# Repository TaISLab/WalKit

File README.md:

# WalKit

WalKit is an open hardware project created to monitor the elderly. It is modular, so different parameters, such as weight-bearing, cadence, activity duration, walking speed or other spatiotemporal gait parameters can be monitoring. 

- Packages in WalKit repository:
    - firmware: arduino codes for handles and wheels. 
    - hardware: 3d models and schematics.
    - walker_arduino: ros2 nodes to interact with USB arduino boards.   
    - walker_bringup: robot specific configuration scripts and tools. 
    - walker_centroid_support: obtains weight centroid based on current support.
    - walker_description: robot description.  
    - walker_diff_odom: odometry node.
    - walker_loads: reports partial supports on each leg.
    - walker_msgs: custom handle and wheel encoder msgs.
    - walker_navigation2: nav2 configuration for walker (TODO). 
    - walker_rviz: draws what the walker measures in rviz (handle loads, feet, support centroid, stability, gait) and holds the rviz views.
    - walker_simulation: roller simulation in gazebo.
    - walker_slam: (TODO)
    - walker_step_detector: reports step position.
    - walker_web_gui: web interface for tests.
            
- Other repositories the workspace uses (all in [`walker.repos`](walker.repos), see [Getting the sources](#getting-the-sources))
    - csm: ROS2 port of Andrea Censi's scan matcher, needed by the laser scan matcher package.
    - ros2_laser_scan_matcher: provides odometry from laser readings.
    - rplidar_ros: RPLidar A1 package.
    - witmotion_ros: driver of the WitMotion IMU.
    - slg_msgs, laser_segmentation: scan segmentation, used by the `seg` variant of walker_step_detector.
    - mocap4r2: MOCAP4ROS2 messages, visualisation and Vicon driver.
    - e4_msgs: messages of the Empatica E4 wristband.

<p align="right">(<a href="#top">back to top</a>)</p>

<!-- GETTING THE SOURCES -->
## Getting the sources

The public repositories the workspace is made of (WalKit itself, the sensor drivers, the laser odometry, the mocap messages...) are
listed in [`walker.repos`](walker.repos), in the native format of [vcstool](https://github.com/dirk-thomas/vcstool). Each key is the
path inside the workspace's `src` folder, and `version` is a branch, a tag or a commit:

```yaml
repositories:
  lidar/rplidar_ros:
    type: git
    url: https://github.com/Slamtec/rplidar_ros.git
    version: ros2
```

To get all of them into an empty workspace (WalKit included, so there is nothing to clone before):
```
sudo apt install python3-vcstool
mkdir -p ~/workspace/walker_ws/src && cd ~/workspace/walker_ws
vcs import src --input https://raw.githubusercontent.com/TaISLab/WalKit/jazzy/walker.repos
```
From a clone of WalKit it is `vcs import src < src/WalKit/walker.repos`. The destination folder (`src`) has to exist already. Then build the
workspace with colcon as usual.

| To... | Run |
|---|---|
| see what changed in every repository | `vcs status src` |
| update them all | `vcs pull src` |
| add the repositories that were added to the file, without touching the ones you have | `vcs import --skip-existing src < walker.repos` |
| download without history | `vcs import --shallow src < walker.repos` |
| check that every url and version of the file exists | `vcs validate --input walker.repos` |
| save the exact commits of your workspace (e.g. for an experiment) | `vcs export --exact src > workspace.repos` |

Things to know:
- **Do not use `--skip-existing` for the first import.** `witmotion_ros` brings an empty `witmotion-uart-qt` folder (its submodule), the file
  has an entry for that path, and `--skip-existing` skips folders that exist: it stays empty and `witmotion_ros` does not build. Use it to
  update, because it also leaves alone the repositories where you have checked out another branch; a plain `vcs import` over a workspace
  switches each repository back to its `version`.
- `witmotion/witmotion_ros/witmotion-uart-qt` is pinned to a commit (the one `witmotion_ros` has as a submodule), which `vcs validate`
  cannot verify without cloning. `--shallow` works with it.
- `vcs` prints a `pkg_resources` deprecation warning with recent setuptools: it is harmless.
- Commented-out entries are the repositories the workspace used before or does not use any more; removing the `#` at the start of their
  lines makes them valid entries.
- The mocap4w analysis tools are in private repositories and are not in this file; they are listed in `mocap4w.repos`, in the
  [mocap_analysis](https://github.com/MFernandezCarmona/mocap_analysis) repository (it needs access to that account). Import it after this one.
- The old `walker.rosinstall` (wstool format) is gone: `wstool` is deprecated and does not read `.repos` files.

<p align="right">(<a href="#top">back to top</a>)</p>

<!-- USAGE EXAMPLES -->
## Usage
The system can be launched with the following:
```
cd ~/workspace/walker_ws/src/WalKit/walker_bringup/tmule/
tmule -c walker.yaml launch
```
Every window of `walker.yaml` has the `core` tag, so `--tag core` starts the same. The session does not record a rosbag: to record one run
`ros2 launch walker_bringup bag_recorder.launch.py bag_name:=test01`: the bag is stored at `~/bagsFolder/<campaign>_tests_walker/test01`
(see [walker_bringup](walker_bringup/README.md#recording-a-test)).

ROS launch files can be monitored at the tmux session. You can attach to it with the following command:
```
tmux a -t walker_ros2
```

You may have noticed we use Marc-Hanheide's [TMuLE](https://github.com/marc-hanheide/TMuLE) program to configure and manage a [tmux](https://github.com/tmux/tmux) session running all the components. TMuLE can be installed with:
```
sudo -H pip3 install tmule
```

<p align="right">(<a href="#top">back to top</a>)</p>

<!-- CONTRIBUTING -->
## Contributing

If you have a suggestion that would make this better, please fork the repo and create a pull request. You can also simply open an issue with the tag "enhancement".
Don't forget to give the project a star! Thanks again!

1. Fork the Project
2. Create your Feature Branch (`git checkout -b feature/AmazingFeature`)
3. Commit your Changes (`git commit -m 'Add some AmazingFeature'`)
4. Push to the Branch (`git push origin feature/AmazingFeature`)
5. Open a Pull Request

<p align="right">(<a href="#top">back to top</a>)</p>

<!-- LICENSE -->
## License

This project is licensed under the Creative Commons Attribution 4.0 - see [LICENSE](https://github.com/TaISLab/WalKit/blob/master/LICENSE) file for details.

<p align="right">(<a href="#top">back to top</a>)</p>

<!-- CONTACT -->
## Contact

Manuel Fernandez-Carmona - [@ermanazas](https://twitter.com/ermanazas) - manolofc at gmail.com

Project Link: [https://github.com/TaISLab/WalKit/tree/humble](https://github.com/TaISLab/WalKit/tree/humble)

<p align="right">(<a href="#top">back to top</a>)</p>

<!-- ACKNOWLEDGMENTS -->
## Acknowledgments

This work is funded by [Programa Proyectos RETOS del Ministerio de Ciencia, Innovación y Universidades (SAVIA: Sistema de Autonomía Variable para movIlidad Asistida, Ref: RTI2018-096701-B-C21)](http://www.grupoisis.uma.es/index.php?option=com_jresearch&view=project&task=show&id=208&Itemid=18&lang=es) at Málaga University, Spain

[Plan Propio de la Universidad de Málaga (E3-PROYECTOS DE PRUEBA DE CONCEPTO (E3/02/18))](https://www.uma.es/servicio-de-investigacion/cms/menu/plan-propio-de-investigacion/?set_language=en) at Málaga University, Spain

This great readme is based on [Othneil Drew](https://github.com/othneildrew/Best-README-Template)'s README template.

<p align="right">(<a href="#top">back to top</a>)</p>

<!-- MARKDOWN LINKS & IMAGES -->
<!-- https://www.markdownguide.org/basic-syntax/#reference-style-links -->
[contributors-shield]: https://img.shields.io/github/contributors/TaISLab/WalKit
[contributors-url]: https://github.com/TaISLab/WalKit/graphs/contributors
[forks-shield]: https://img.shields.io/github/forks/TaISLab/WalKit
[forks-url]: https://github.com/TaISLab/WalKit/network/members
[stars-shield]: https://img.shields.io/github/stars/TaISLab/WalKit
[stars-url]: https://github.com/TaISLab/WalKit/stargazers
[issues-shield]: https://img.shields.io/github/issues/TaISLab/WalKit
[issues-url]: https://github.com/TaISLab/WalKit/issues
[license-shield]: https://img.shields.io/github/license/TaISLab/WalKit
[license-url]: https://github.com/TaISLab/WalKit/blob/master/LICENSE
[product-screenshot]: images/screenshot.png

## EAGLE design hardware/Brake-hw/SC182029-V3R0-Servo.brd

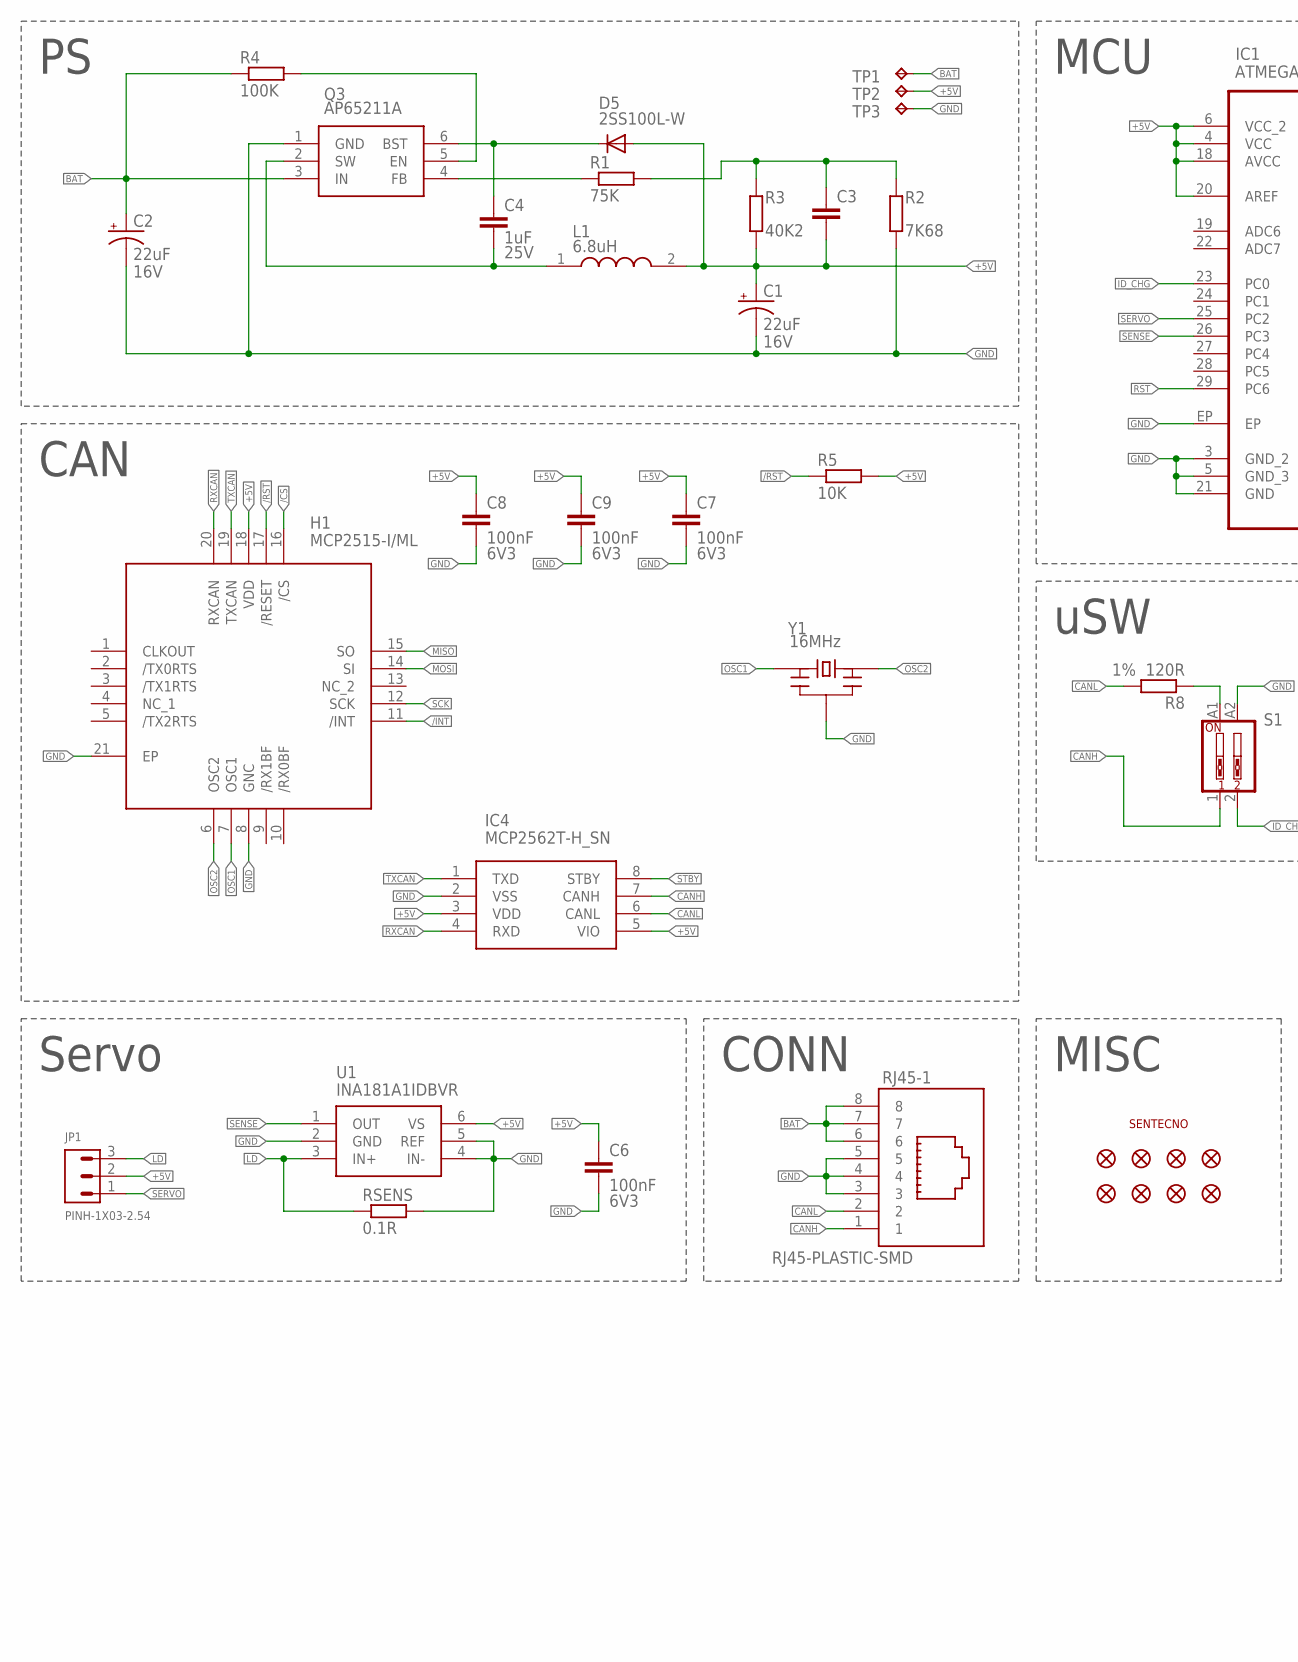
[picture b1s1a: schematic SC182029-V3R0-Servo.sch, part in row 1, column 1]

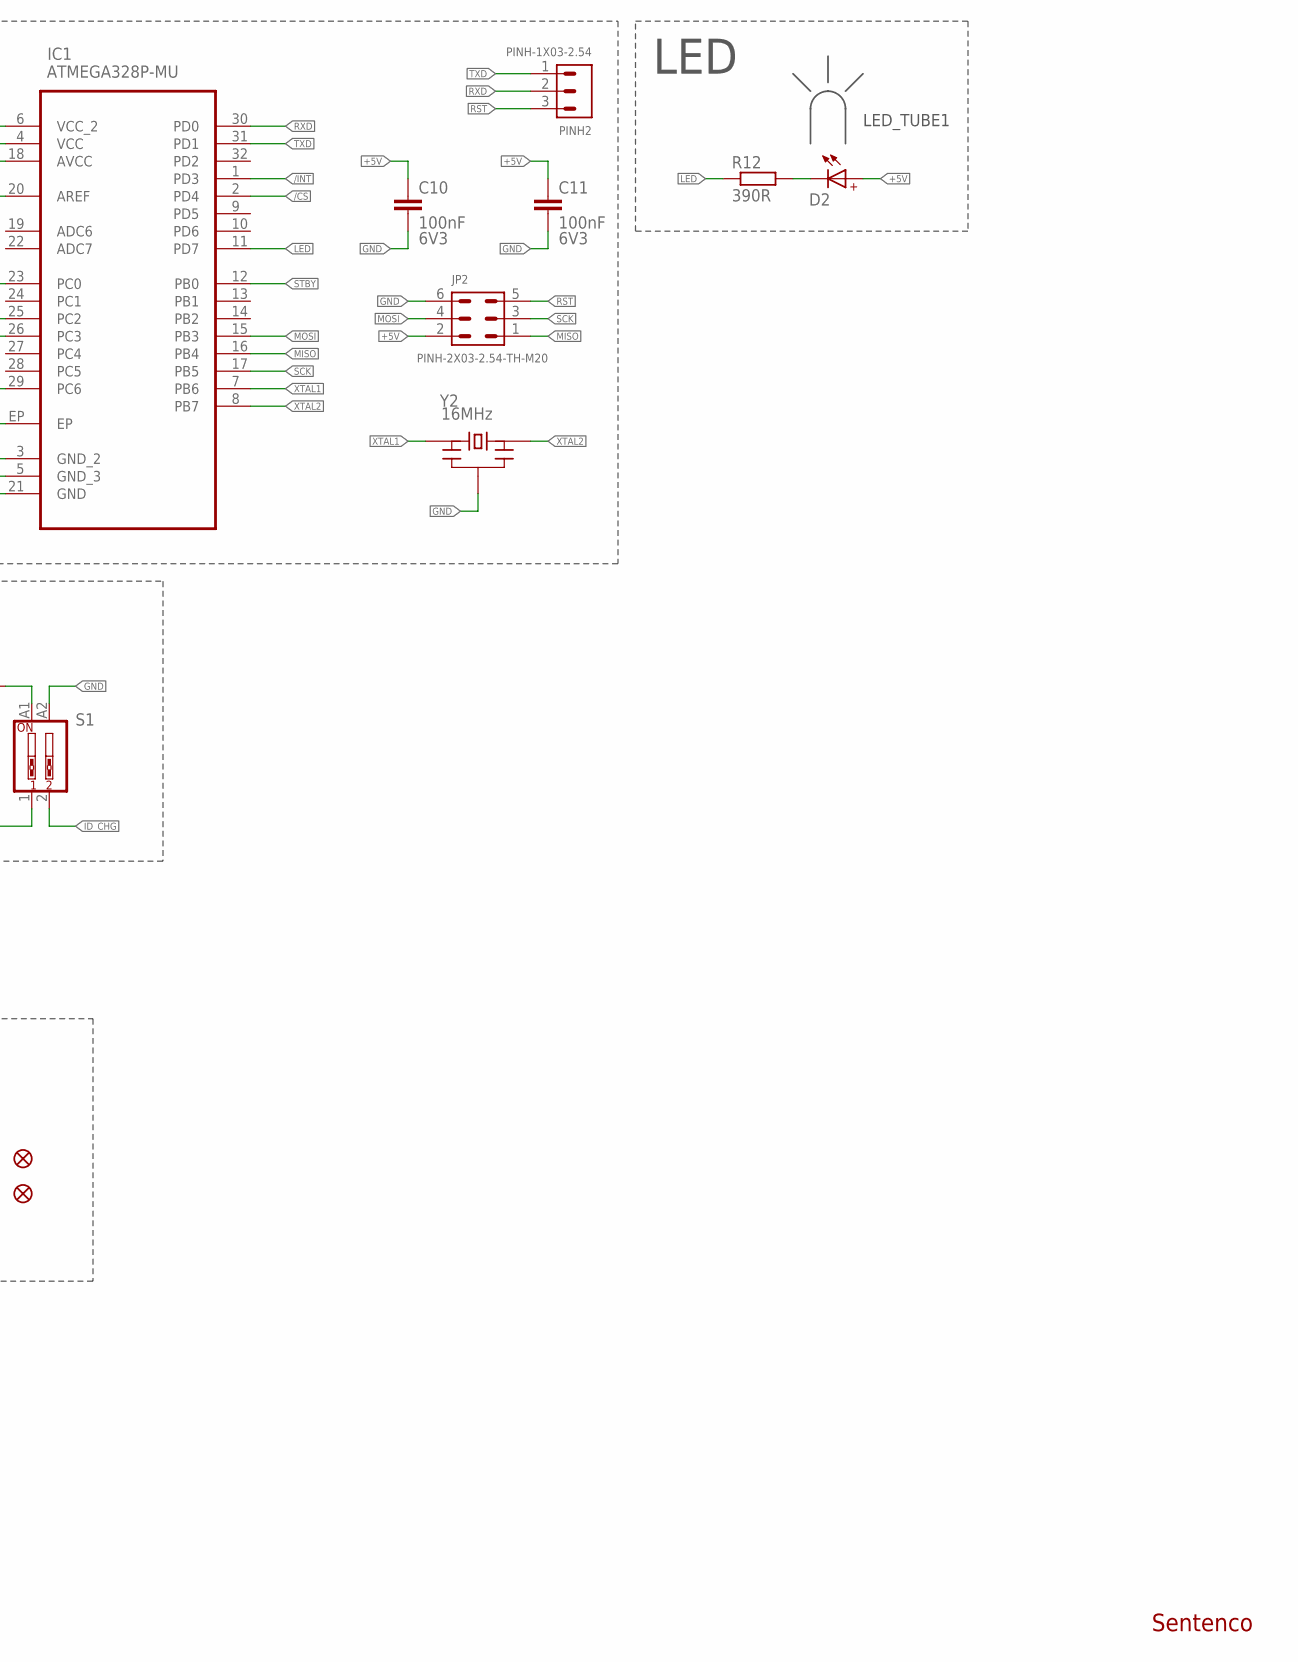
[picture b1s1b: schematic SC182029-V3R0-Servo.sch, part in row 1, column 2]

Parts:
C1, C2: 22uF; B
C3: COND_CERAMICO_SMD0603R; C0603R
C4: 1uF; C0603R
C6, C7, C8, C9, C10, C11: 100nF; C0603R
D2: WL-SMCW-150060BS75000; WL-SMCW_0603
D5: 2SS100L-W; SOD-123FL-CUSTOM
FID1, FID2, FID3, FID4, FID5, FID6, FID7, FID8: FIDUCIALUFIDUCIAL; MICRO-FIDUCIAL
H1: MCP2515-I/ML; QFN50P400X400X90-21N
IC1: ATMEGA328P-MU; QFN50P500X500X100-33N
IC4: MCP2562T-H_SN; SOIC127P600X175-8N
JP1: PINH-1X03-2.54; PINH-1X03-2.54-1
JP2: PINH-2X03-2.54-TH-M20; HDRV6W64P254_2X3_762X508X868P
L1: 6.8uH; NR5040
LED_TUBE1: LED_TUBEH1; LED_TUBE_2
LOGO1: LOGO_SENTECNOLOGO_6X4MM; LOGO_6X4MM
PINH2: PINH-1X03-2.54; PINH-1X03-2.54-1
Q3: AP65211A; SOT95P280X90-6N
R1: 75K; R0603R
R2: 7K68; R0603R
R3: 40K2; R0603R
R4: 100K; R0603R
R5: 10K; R0603R
R8: 120R; R0603R
R12: 390R; R0603R
RJ45-1: RJ45-PLASTIC-SMD; 73304111LF
RSENS: 0.1R; R0603R
S1: DIP-SW-2; SMD-DIP-SWITCH-2P
TP1, TP2, TP3: TPTP08R; TP0.8MMR
U1: INA181A1IDBVR; SOT95P280X145-6N
Y1, Y2: 16MHz; CSTNE16M0V530000R0

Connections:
+5V: C1.PIN_1_POS (+), C3.2, C6.1, C7.1, C8.1, C9.1, C10.1, C11.1, D2.2 (+), D5.+ (A), H1.18 (VDD), IC1.4 (VCC), IC1.6 (VCC_2), IC1.18 (AVCC), IC1.20 (AREF), IC4.3 (VDD), IC4.5 (VIO), JP1.2, JP2.2, L1.2, R3.1, R5.2, TP2.TP, U1.6 (VS)
/CS: H1.16 (/CS), IC1.2 (PD4)
/INT: H1.11 (/INT), IC1.1 (PD3)
/RST: H1.17 (/RESET), R5.1
BAT: C2.PIN_1_POS (+), Q3.3 (IN), R4.1, RJ45-1.6, RJ45-1.7, RJ45-1.8, TP1.TP
CANH: IC4.7 (CANH), RJ45-1.1, S1.1
CANL: IC4.6 (CANL), R8.2, RJ45-1.2
GND: C1.PIN_2_NEG (-), C2.PIN_2_NEG (-), C6.2, C7.2, C8.2, C9.2, C10.2, C11.2, H1.8 (GNC), H1.21 (EP), IC1.3 (GND_2), IC1.5 (GND_3), IC1.21 (GND), IC1.EP, IC4.2 (VSS), JP2.6, Q3.1 (GND), R2.1, RJ45-1.3, RJ45-1.4, RJ45-1.5, RSENS.2, S1.A2, TP3.TP, U1.2 (GND), U1.4 (IN-), U1.5 (REF), Y1.2 (GND), Y2.2 (GND)
ID_CHG: IC1.23 (PC0), S1.2
LD: JP1.3, RSENS.1, U1.3 (IN+)
LED: IC1.11 (PD7), R12.1
MISO: H1.15 (SO), IC1.16 (PB4), JP2.1
MOSI: H1.14 (SI), IC1.15 (PB3), JP2.4
unnamed: R8.1, S1.A1
unnamed: Q3.5 (EN), R4.2
unnamed: C4.1, D5.- (K), D5.-- (K), Q3.6 (BST)
unnamed: C4.2, L1.1, Q3.2 (SW)
unnamed: D2.1 (-), R12.2
unnamed: Q3.4 (FB), R1.1
unnamed: C3.1, R1.2, R2.2, R3.2
OSC1: H1.7 (OSC1), Y1.3 (OUT)
OSC2: H1.6 (OSC2), Y1.1 (IN)
RST: IC1.29 (PC6), JP2.5, PINH2.3
RXCAN: H1.20 (RXCAN), IC4.4 (RXD)
RXD: IC1.30 (PD0), PINH2.2
SCK: H1.12 (SCK), IC1.17 (PB5), JP2.3
SENSE: IC1.26 (PC3), U1.1 (OUT)
SERVO: IC1.25 (PC2), JP1.1
STBY: IC1.12 (PB0), IC4.8 (STBY)
TXCAN: H1.19 (TXCAN), IC4.1 (TXD)
TXD: IC1.31 (PD1), PINH2.1
XTAL1: IC1.7 (PB6), Y2.3 (OUT)
XTAL2: IC1.8 (PB7), Y2.1 (IN)

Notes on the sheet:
LED
MCU
Servo
CONN
CAN
MISC
uSW
Sentenco

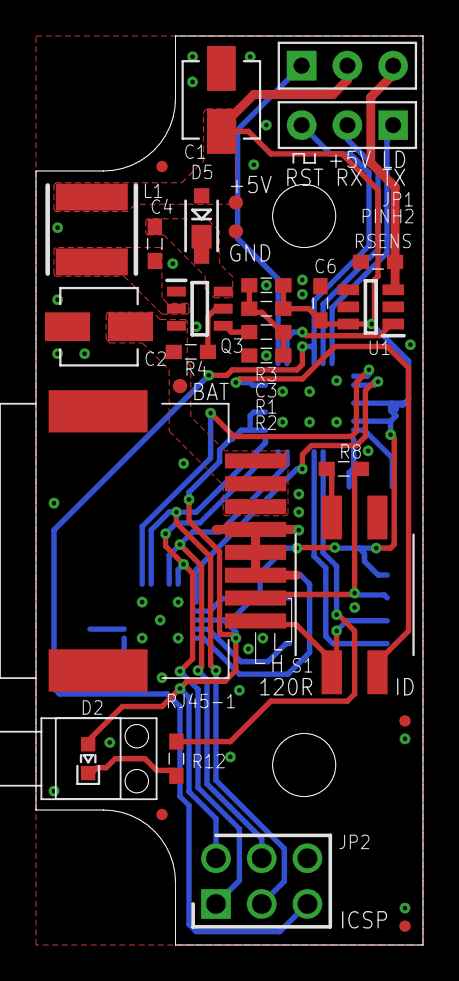
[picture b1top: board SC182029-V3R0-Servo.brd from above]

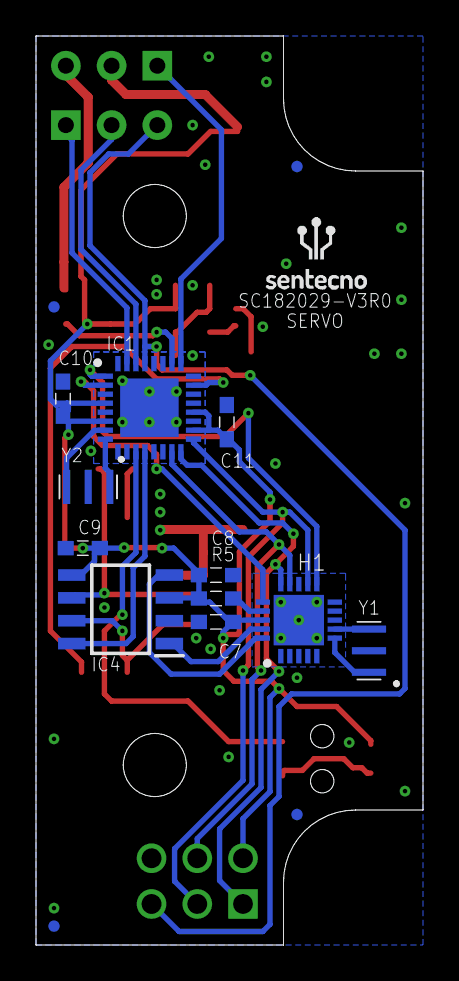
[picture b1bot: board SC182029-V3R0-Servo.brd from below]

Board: 2 copper layers, 21.5 x 50.5 mm, 46 parts (16 on the bottom side), 33 nets.

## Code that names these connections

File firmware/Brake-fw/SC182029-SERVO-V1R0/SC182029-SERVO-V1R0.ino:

/* ================================================================

   Proyecto: Modulo de encoder en andador para UMA
   Placa de desarrollo: Arduino
   Función: Gira entre 0 y 90 grados la posición del servo empujando
			el cable de freno, tiene un led indicador y envía los datos a
			través del BUS CAN.
			
   Autor: Justo Barroso Fontalba
   Fecha: 19/03/2019

   ================================================================ */

/* ================================================================
   Librerías
   ================================================================ */

#include <SPI.h>
#include <Servo.h>
#include <mcp_can.h>

/* ================================================================
   Definición de pines
   ================================================================ */

//ATMega328 TQFP
//                    Pin IDE //Pin puerto, Pin Físico
#define LED_GATE        7     //PD7, 11
#define MCP2515_STBY    8     //PB0, 12
#define MCP2515_CS      4     //PD4, 2
#define MCP2515_INT     3     //PD3, 1
#define SERVO           16    //PC2, 25
#define SENSE           17    //PC3, 26
#define ID_CHG          14    //PC0, 23
//#define MCP2515_SI      11    //PB3, 15
//#define MCP2515_SO      12    //PB4, 16
//#define MCP2515_SCK     13    //PB5, 17

//Test en Arduino UNO
//#define MCP2515_CS      10
//#define MCP2515_INT     2
//#define SERVO           3       //PD3, 5  (Arduino UNO)

//Constantes
#define ID_RIGHT      0x013   //Identificador del modulo derecho
#define ID_LEFT       0x023   //Identificador del modulo izquierdo
#define MAX_CURRENT   715     //Valor máximo de corriente en el servo 1.75A

/* ================================================================
   Definición de funciones
   ================================================================ */

/* ================================================================
   Definición de estructuras
   ================================================================ */

/* ================================================================
   Definición de variables
   ================================================================ */

static long unsigned int rxId; //Identificador del mensaje
static byte len = 0; //Longitud del mensaje
static byte rxBuf[8]; //Array datos de recepción
static byte txBuf[8] = { 0x00, 0x00, 0x00, 0xDD, 0x00, 0xFF, 0x00, 0x00 }; //Array datos de envió
static byte id_device = ID_LEFT;

/* ================================================================
   Drivers
   ================================================================ */

Servo servoMotor;

/* ================================================================
   Inicialización
   ================================================================ */

MCP_CAN CAN0( MCP2515_CS ); // Establece el CS en el pin 10

void setup() {
  //Configuración de pines
  pinMode( LED_GATE, OUTPUT );
  pinMode( SENSE, INPUT );
  pinMode( MCP2515_INT, INPUT_PULLUP ); // Interrupción MCP2515
  pinMode( MCP2515_STBY, OUTPUT ); // CS MCP2515  
  pinMode( ID_CHG, INPUT_PULLUP ); // Selección izquierda/derecha
  digitalWrite( MCP2515_STBY, LOW ); // Modo normal activo MCP2562

  //Establece la posición del modulo en el andador
  if ( digitalRead( ID_CHG ) == 0 ) {
    id_device = ID_RIGHT;
  }

  //Inicialización de puerto serie
  Serial.begin( 115200 );

  //Inicialización MCP2515, mascara y filtros activados, velocidad 500kb/s, cristal 16MHz
  if ( CAN0.begin( MCP_STDEXT, CAN_500KBPS, MCP_16MHZ ) == CAN_OK ) {
    Serial.println( "MCP2515 Initialized Successfully!" );
  }
  else {
    Serial.println( "Error Initializing MCP2515..." );
  }

  //Establece mascaras y filtros para los dispositivos
  CAN0.init_Mask( 0, 0, 0x001F0000 ); // Iniciando primera mascara
  CAN0.init_Filt( 0, 0, 0x00100000 ); // Iniciando primer filtro, ID 0x10 (rPi)

  CAN0.init_Mask( 1, 0, 0x001F0000 ); // Iniciando segunda mascara

  //Configuración del MCP2515
  CAN0.setMode( MCP_NORMAL ); // Modo normal para permitir el envio de mensajes

  //Configuración de pines
  servoMotor.attach( SERVO );

  //Establecer el angulo a 0
  servoMotor.write( 150 );

  //Configurando la interrupción por pin
  attachInterrupt( digitalPinToInterrupt( MCP2515_INT ), readCAN, LOW );

  for (int i = 0; i < 3; i++)
  {
    digitalWrite( LED_GATE, LOW );
    delay(200);
    digitalWrite( LED_GATE, HIGH );
    delay(200);
  }
}

/* ================================================================
   Bucle principal
   ================================================================ */

void loop() {
  
}

/* ================================================================
   Interrupciones
   ================================================================ */

void readCAN() {
  CAN0.readMsgBuf( &rxId, &len, rxBuf ); // Leer datos: len = longitud de los datos, buf = bytes de datos
  if ( rxBuf[0] == id_device ) {
    if ( ( rxBuf[1] & 0b00000001 ) == 0b00000001 ) {
      //if ( ( PIND & B10000000 ) == B00000000 ) {
        digitalWrite( LED_GATE, LOW ); //Enciende el LED
        Serial.println( "Led encendido" );
      //}
    }
    if ( ( rxBuf[1] & 0b00000001 ) == 0b00000000 ) {
      //if ( ( PIND & B10000000 ) == B00000100 ) {
        digitalWrite( LED_GATE, HIGH ); //Apaga el LED
        Serial.println( "Led apagado" );
      //}
    }
    //Rango operativo del servo entre 70 y 150 o 0x46 (90 grados) y 0x96 (0 grados)
    if ( ( rxBuf[1] & 0b00000010 ) == 0b00000010 ) {
      if ( rxBuf[2] <= 0x96 && rxBuf[2] >= 0x46 ) {
        servoMotor.write( rxBuf[2] ); //valor al servo
        //Serial.println( analogRead( SENSE ) );
        while ( analogRead( SENSE ) >= MAX_CURRENT ) {
          servoMotor.write( rxBuf[2] -= 0x05 );
          Serial.println( "Se ha reducido la fuerza ejercida sobre el freno." );
        }        
      }
      Serial.println( "Valor establecido: " );
      Serial.println( rxBuf[2] );
    }
  }
}

/* ================================================================
   Funciones
   ================================================================ */

/* ================================================================
   Fin
   ================================================================ */

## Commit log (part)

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2020-02-11 Create LICENSE
2021-11-22 WIP: sorting out new ros2 - foxy branch - created msg for Handle forces - created usb publisher node with launcher (TODO: parametrise published data int/double) TODO: upload Arduino codes for handles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
2021-11-24 WIP! - walker_arduino - reads data from usb arduinos and publishes it - TODO: - TEST!
    - walker_bringup
    - main package to start robot/spawn simulated robot
    - should call to walker_description, diff_odom, handles, lidars, etc ...
    - TODO:
    - think possible migration to param file
    - finish udev rules to ease serial port access
2021-11-24 added simulated worlds
2021-11-24 New arduino codes. Removed windows garbage
2021-11-24 First working version of Arduino devices
2021-11-25 m.ch.
2021-11-25 Removed submodule. It's easier to use separated repos
2021-11-29 limited number of tested chars
2021-11-29 debug info added
2021-11-29 Changed from stream buffers to use timeouts
2021-11-29 Can't find elegant solution to autodiscovery
2021-11-29 adding stuff
2021-11-29 WIP: walker_diff_odom
2021-11-30 Each device has now an udev rule for easier launch
2021-11-30 parameters adjusted but left wheel is still quite faulty
2021-11-30 laser launch file with custom params
2021-12-01 Rosinstall file added
2021-12-10 WIP: fixing odometry
2021-12-10 diff_odom: working version bringup: - tmule script also records data now - lasers are filtered for self collisions
2021-12-13 Added record to tmule script Added simple force plotter
2021-12-14 - Added config for laser filtering out leg detections - Added tmule file tags to avoid default recording - Added mapper config
2021-12-14 added reasonable tf for leapmotion
2021-12-16 typo
2021-12-17 Added leg detector repo
2021-12-17 Added laser_filters
2021-12-20 Filters is forked to support "inside box" filters
2021-12-20 added leg detector
2021-12-21 fire
2022-01-12 Odometry hardware was in wrong place
2022-01-16 Added detected steps to tmule file Removed bag reader script for more specific ones with plotting Created bag replay launchers to create additional topic bags
2022-01-17 WIP: partial load analysis
2022-01-17 first attempt for partial load node
2022-01-18 Better analysis pipeline
2022-01-19 Sorting and creating plotter
2022-01-24 WIP: playing with plot loads...
2022-01-26 MAYOR CHANGES! - no more leg_detector_msgs. Now all in walker_msgs - one topic per step, no more arrays - moved step_detector to Walkit and renamed to walker_step_detector
2022-01-26 params
2022-02-01 laser filter changed
2022-02-01 cleaning
2022-02-02 initial config
2022-02-08 Added vanilla odometry error
2022-02-08 bug including eigen
2022-02-08 adding covariance to odometry
2022-02-15 working on new odom and gait params
2022-02-16 bugs
2022-02-17 recording leapmotion too
2022-02-18 Working on gait param analysis
2022-03-09 ROS2 new version
2022-04-04 Demo changes
2022-04-04 m.ch
2022-04-06 Corrected handle position in crappy yaml Commented Step msg Added weight centroid calculus in partial loads
2022-05-04 WIP: including kalman filter for leg tracking
2022-05-05 working on kalman
2022-05-09 WIP: improve TF tree
2022-05-09 WIP: centroid module
2022-05-10 kalman filter embedded into step detector. Not ideal, but it works
2022-05-10 Added markers for visualization ...
2022-05-11 added csv debug output: we are detecting far few clusters...
2022-05-16 laser filters and leg detector removed
2022-05-16 Checking lsm
2022-05-16 Removing binaries from repo
2022-05-16 lcm works. EKF is not reading data for some reason ...
2022-05-17 friday
2022-05-17 Looks like it's working now
2022-05-18 debug prints commented
2022-05-18 All seems to work, but rviz debug is laggy
2022-05-19 testing centroid module
2022-05-20 centroid support module done
2022-05-23 WIP: Gui improvement
2022-05-23 Enc odom is no longer default
2022-05-23 improving tf
2022-05-23 mch2
2022-05-23 New robot model. New tf tree. New gui. Needs some testing
2022-06-10 Almost there
2022-06-13 First working version
2022-06-14 load detector with kalman filter seems to be working
2022-06-15 User description as a latched topic
2022-06-16 added modules to yaml
2022-06-21 python nodes now don't overreact to Ctrl+C Handle calibration only present at walker_loads. New msgs for gait params
2022-06-29 rule with all sensors
2022-07-04 Fixing install deps. Adding vars to gui. Publishing config data periodically
2022-07-04 did I messed it again?
2022-07-19 WIP: improving representation
2022-07-21 WIP: working on demo view
2022-07-21 WIP: less verbose output while waiting for all data
2022-07-21 Less verbose output. TF is published every 500ms
2022-07-21 Added handle load publisher (kg)
2022-07-21 Added live plot with - leg position (with loads) - laser in active area - handles (with loads)
2022-07-21 Publishing a stampedPose list of laser points to be used in gui. Active area is now filtered by step detector itself. Adding kalman multiple clusters adds half and half.
2022-07-21 added library
2022-07-21 ouch
2022-07-21 laser mask adjusted
2022-07-21 (rough) Motion vector added to visualization
2022-07-25 check size first
2022-07-25 added usb cam config
2022-09-07 IMU relocated over the laser sensor
2022-09-07 Added IMU data to web status
2022-09-07 rounded imu angles
2022-09-13 ref added
2022-09-26 After adjusting laser some points needed to be masked
2022-12-22 wheel encoder broken. Not recording it now
2023-02-19 compila
2023-02-21 km naive working with easy situations
2023-02-23 clearing debug msgs
2023-03-20 minor tweaking
2023-03-22 rosinstall updated
2023-04-13 first code
2023-04-14 Faltan gaussiana y combinacion de capas
2023-04-17 lorito
2023-04-17 walker.yaml
2023-04-17 ignore simulation
2023-04-17 Changed AS5601 library with AS5600
2023-04-17 compila. listo para probar
2023-04-18 WIP: - user stabilitiy node. - renamed topics in stability gridmap - added tinetti into web_gui (and queues set to 0 for performance) - corrected error in walker_loads
2023-04-21 walker_stability/
2023-04-21 Ready for test with rosbags
2023-04-24 paquetes de solo configuraciones eliminados. nuevo laser filtrado solo para navegacion
2023-04-26 clock recorded. map configured by cfg
2023-05-09 mierda de tarde
2023-05-11 walker stability works. now get stability gridmap
2023-05-12 we can generate maps
2023-05-13 images!
2023-05-15 added dummy user
2023-05-16 cosas de Joaquin
2023-05-16 no se programar
2023-05-16 joaquin changes
2023-07-04 walker_usb_cameras package added
2023-07-06 stereo camera added
2023-10-05 WIP: adding d435 and new imu sw to system
2023-10-05 useful
2023-10-06 going for v3
2023-10-09 solved librealsense not publishing both images
2023-10-09 dont record compressed topics
2023-10-20 testing stereo viso
2023-10-20 fused odom working
2023-10-20 efk in progress
2024-03-06 laser_filter_generator
2024-03-07 - changed to ros2 branch of the official rplidar repo - moved tmule config files to its own folder - changed imu node to achieve 100Hz - WIP: ekf odometry fusion
2024-03-18 new filters
2024-04-15 Added Jesus camera
2025-03-05 Cleaning error messages
2026-05-12 Firs compiling version for Rpi5

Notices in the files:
README.md:
License: CC BY 4.0
